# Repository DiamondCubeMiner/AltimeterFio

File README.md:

# AltimeterFio
A SparkFun BME280 board backpack for Arduino Fio

This board adapts the [SparkFun BME280](https://github.com/sparkfun/SparkFun_BME280_Breakout_Board) to an [Arduino Fio](https://github.com/sparkfun/Arduino_Fio).
The board is intended to be mounted to the back of the Arduino Fio, at the same side where the XBee is mounted.

The board allows the Fio to become an Altimeter with downlink. A microcontroller on the ground will be able to get the sensor data wirelessly through XBee, and calculate the altitude.
The entire system will be used on my future rocketry projects, but can be easily adapted with model aircraft and other UAV.

## Libraries
Since this board is basically an extension of the SparkFun BME280, it should work with the same library as the original.
* [SparkFun BME280 Library](https://github.com/sparkfun/SparkFun_BME280_Arduino_Library)

## Thanks
Big thanks to [SparkFun](https://github.com/sparkfun) for providing Open Source documentation to their BME280 board.
I added a SparkFun logo on the board as a token of gratitude.

## License
This work is licensed under the Creative Commons Attribution-ShareAlike 4.0 International License. To view a copy of this license, visit http://creativecommons.org/licenses/by-sa/4.0/ or send a letter to Creative Commons, PO Box 1866, Mountain View, CA 94042, USA.

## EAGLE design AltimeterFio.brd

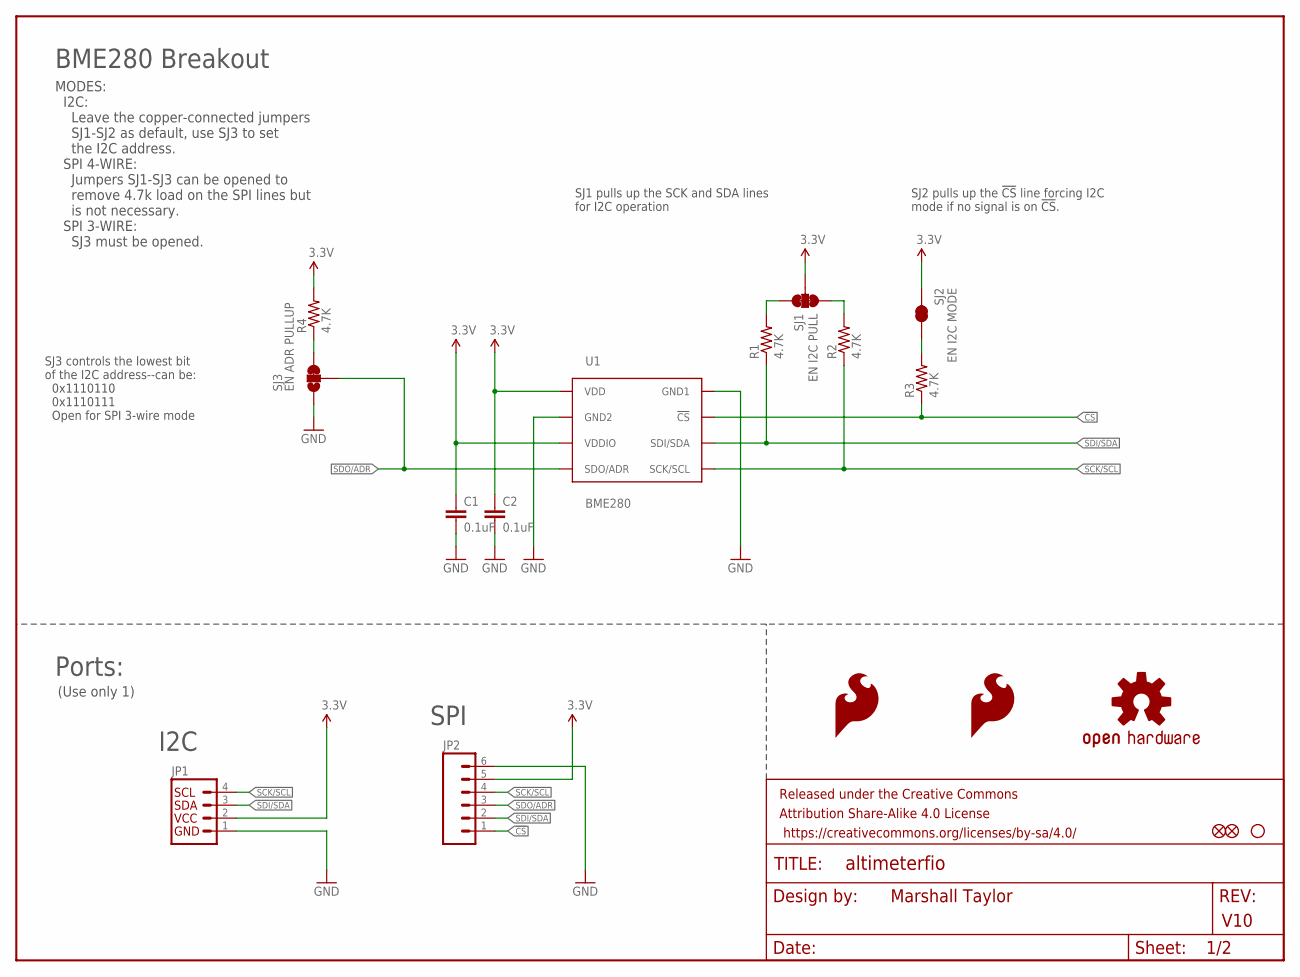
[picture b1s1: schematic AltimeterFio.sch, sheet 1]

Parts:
C1, C2: 0.1uF; 0603-CAP
FID1, FID2: FIDUCIAL1X2; FIDUCIAL-1X2
FRAME1: FRAME-LETTER; CREATIVE_COMMONS
JP1: I2C_STANDARD_NO_SILK; 1X04_NO_SILK
JP2: M06NO_SILK_FEMALE_PTH; 1X06_NO_SILK
LOGO1, LOGO2: SFE_LOGO_FLAME.1_INCH; SFE_LOGO_FLAME_.1
LOGO3: OSHW-LOGOS; OSHW-LOGO-S
R1, R2, R3, R4: 4.7K; 0603-RES
SJ1: EN I2C PULL; PAD-JUMPER-3-3OF3_NC_BY_TRACE_YES_SILK_FULL_BOX
SJ2: EN I2C MODE; PAD-JUMPER-2-NC_BY_TRACE_YES_SILK
SJ3: EN ADR PULLUP; PAD-JUMPER-3-2OF3_NC_BY_TRACE_YES_SILK_FULL_BOX
STANDOFF4: STAND-OFF
U1: BME280; BME280_LGA

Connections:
3.3V: C1.1, C2.1, JP1.2, JP2.5, R4.2, SJ1.2, SJ2.2, U1.P$6 (VDDIO), U1.P$8 (VDD); also elsewhere on the board
!CS: JP2.1, R3.1, U1.P$2 (!CS); also elsewhere on the board
GND: C1.2, C2.2, JP1.1, JP2.6, SJ3.1, U1.P$1 (GND1), U1.P$7 (GND2); also elsewhere on the board
unnamed: R1.2, SJ1.3
unnamed: R2.2, SJ1.1
unnamed: R3.2, SJ2.1
unnamed: R4.1, SJ3.3
SCK/SCL: JP1.4, JP2.4, R2.1, U1.P$4 (SCK/SCL); also elsewhere on the board
SDI/SDA: JP1.3, JP2.2, R1.1, U1.P$3 (SDI/SDA); also elsewhere on the board
SDO/ADR: JP2.3, SJ3.2, U1.P$5 (SDO/ADR); also elsewhere on the board

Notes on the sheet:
Marshall Taylor
V10
BME280 Breakout
SJ3 controls the lowest bit of the I2C address--can be: 0x1110110 0x1110111 Open for SPI 3-wire mode
SJ1 pulls up the SCK and SDA lines for I2C operation
Ports:
(Use only 1)
I2C
SPI
MODES: I2C: Leave the copper-connected jumpers SJ1-SJ2 as default, use SJ3 to set the I2C address. SPI 4-WIRE: Jumpers SJ1-SJ3 can be opened to remove 4.7k load on the SPI lines but is not necessary. SPI 3-WIRE: SJ3 must be opened.
SJ2 pulls up the !CS! line forcing I2C mode if no signal is on !CS!.

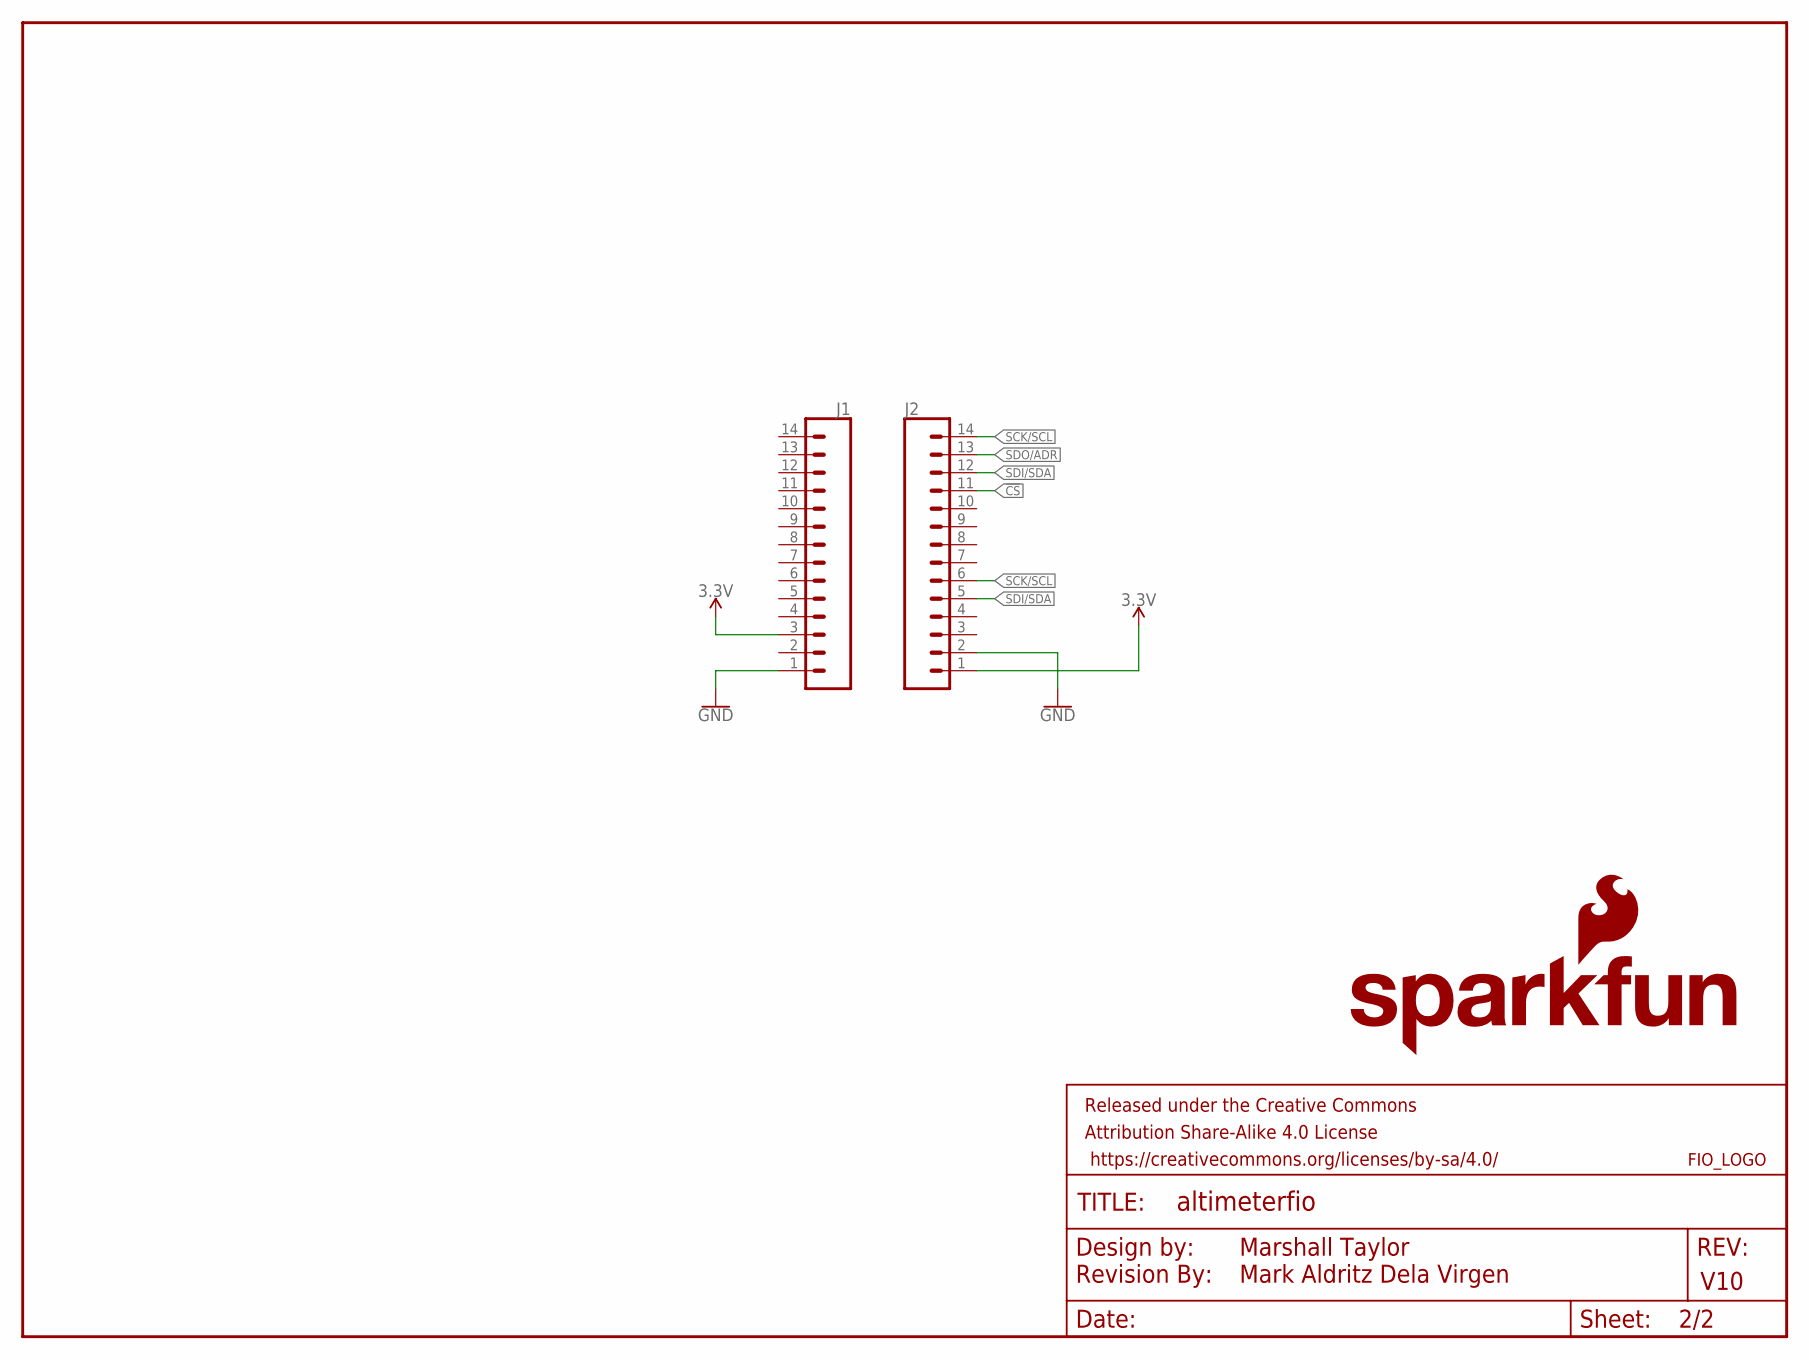
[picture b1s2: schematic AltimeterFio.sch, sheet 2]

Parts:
FRAME2: FRAME-LETTERNO_PACKAGE; DUMMY
J1, J2: CONN_14; 1X14
LOGO4: FIO_LOGOV2; FIO_LOGO
LOGO5: REVISION
LOGO6: SFE_LOGO_NAME_FLAME.1_INCH; SFE_LOGO_NAME_FLAME_.1

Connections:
3.3V: J1.3, J2.1; also elsewhere on the board
!CS: J2.11; also elsewhere on the board
GND: J1.1, J2.2; also elsewhere on the board
SCK/SCL: J2.6, J2.14; also elsewhere on the board
SDI/SDA: J2.5, J2.12; also elsewhere on the board
SDO/ADR: J2.13; also elsewhere on the board

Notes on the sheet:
Marshall Taylor
Mark Aldritz Dela Virgen
V10

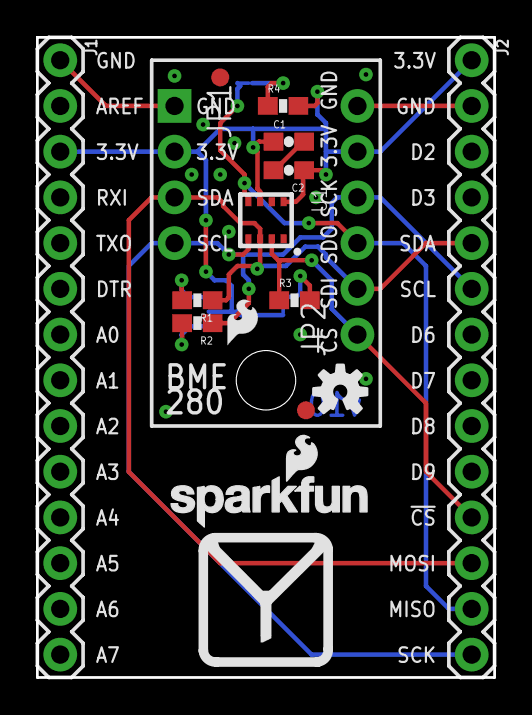
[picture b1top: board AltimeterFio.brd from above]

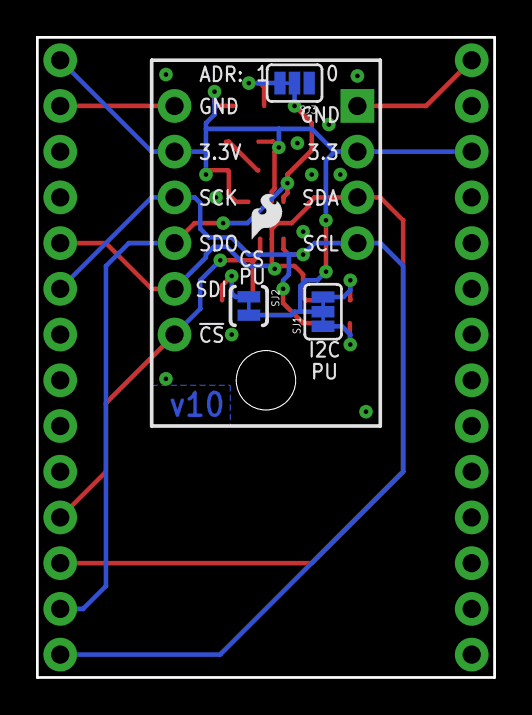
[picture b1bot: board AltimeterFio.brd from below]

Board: 2 copper layers, 25.4 x 35.6 mm, 25 parts (5 on the bottom side), 10 nets.

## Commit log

2021-04-09 Initial upload

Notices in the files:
parts and their libraries:
SparkFun-Capacitors: Licensing: Creative Commons ShareAlike 4.0 International - https://creativecommons.org/licenses/by-sa/4.0
SparkFun-Aesthetics: Released under the Creative Commons Attribution Share-Alike 4.0 License
SparkFun-Aesthetics: https://creativecommons.org/licenses/by-sa/4.0
